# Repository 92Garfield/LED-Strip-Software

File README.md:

# gLED — WLAN LED Strip

NeoPixel strip on a Raspberry Pi Pico W (CircuitPython 9), controlled via browser extension.

## Folders

- `firmware/GEdge` — CIRCUITPY drive content (kitchen strip, 150 LEDs, `192.168.2.42`)
- `gLED-Client Chrome` — Chrome extension, **source of truth** for client `js/` + `css/`
- `gLED-Client Firefox` — Firefox extension (desktop + Android), only `manifest.json` differs
- `client/GEdge-html` — old on-controller web client (retired, kept for reference)

## Firmware (`firmware/GEdge`)

- Copy `src/config.example.py` to `src/config.py`, then set WiFi, IP, LED count, name, physical layout, and default animation
- `src/led_server.py` — HTTP server; serves one tiny HTML page exposing global `gLED`
- `src/animation_runner.py` — non-blocking animation loop beside the server
- `animations/*.py` — one class `Animation` per file (`start(now)` / `step(now)`)
  - `hue_cycle` — whole strip, hue rotates (interval + step configurable)
  - `fill_runner` — red runner right→left stacks until full, then back to blue
- `glib/color.py` — `hsv_to_rgb()` for NeoPixel
- Boot: connects WiFi, starts server, autostarts `config.DEFAULT_ANIMATION`

## HTTP API (`POST /data`, urlencoded, values NOT percent-encoded)

- `type=set` `data=r,g,b|r,g,b|…` — set all pixels (stops animation)
- `type=brightness` `data=1..100`
- `type=animation` `data=<name>` or `data=stop`
- `GET /` — HTML with `var gLED = {name, ledCount, length, physical, animations}`

## Clients (extensions)

- Run on the controller page, replace it entirely with their own UI
- Custom elements (`js/elements/`), built by `js/app.js`, dark CSS
- Show physical layout (y-up), tabs: Animation / Manual (tap LEDs to paint)
- No live data from server; last set state kept in `localStorage`
- Brightness slider in header

### Chrome

- `chrome://extensions` → Developer mode → Load unpacked → `gLED-Client Chrome`

### Firefox (desktop + Android)

- After client changes: run `gLED-Client Firefox/sync.ps1` (copies `js/`+`css/` from Chrome)
- Desktop test: `about:debugging` → Load Temporary Add-on
- Android: needs signed `.xpi` via addons.mozilla.org (unlisted) — see `gLED-Client Firefox/README.md`

## New controller / IP change

Update the IP in **3 places**:

- `gLED-Client Chrome/manifest.json` → `matches`
- `gLED-Client Firefox/manifest.json` → `matches` **and** `host_permissions`
- Firmware: `src/config.py` → `STATIC_IP`

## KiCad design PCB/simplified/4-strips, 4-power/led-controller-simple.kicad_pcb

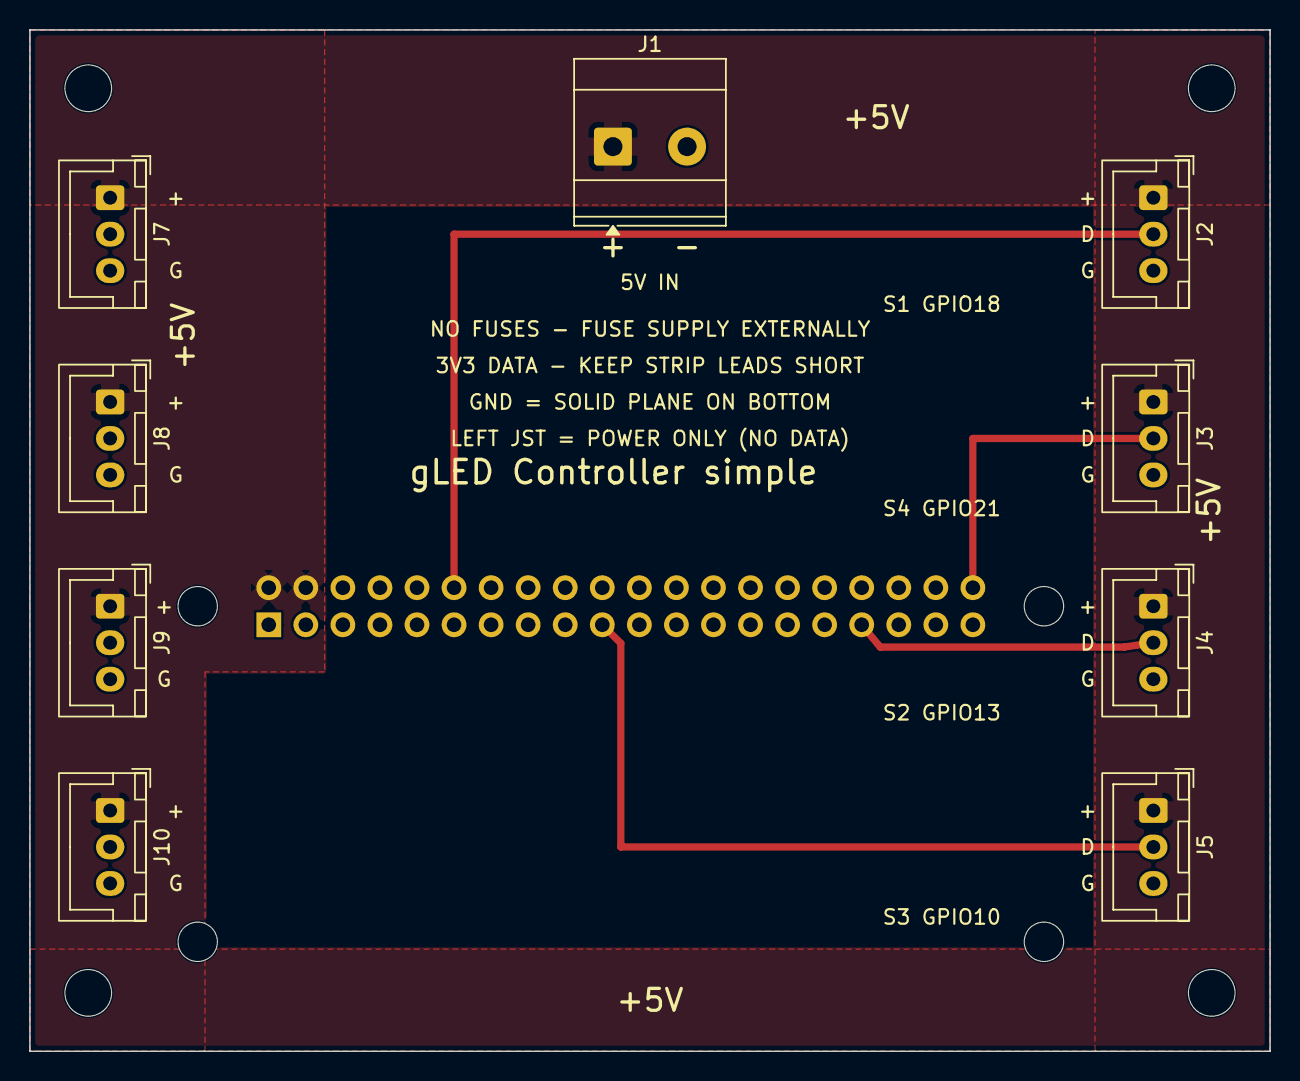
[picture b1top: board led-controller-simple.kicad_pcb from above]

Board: 2 copper layers, 85.0 x 70.0 mm, 18 parts (1 on the bottom side), 6 nets.

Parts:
H1, H2, H3, H4: MountingHole_2.7mm_M2.5
H5, H6, H7, H8: MountingHole_3.2mm_M3
J1: 5V IN; TerminalBlock_Phoenix_MKDS-3-2-5.08_1x02_P5.08mm_Horizontal
J2: GPIO18; JST_XH_B3B-XH-A_1x03_P2.50mm_Vertical
J3: GPIO21; JST_XH_B3B-XH-A_1x03_P2.50mm_Vertical
J4: GPIO13; JST_XH_B3B-XH-A_1x03_P2.50mm_Vertical
J5: GPIO10; JST_XH_B3B-XH-A_1x03_P2.50mm_Vertical
J6: Pi Zero 2 WH; PinSocket_2x20_P2.54mm_Vertical
J7, J8, J9, J10: PWR; JST_XH_B3B-XH-A_1x03_P2.50mm_Vertical

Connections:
+5V: J1.1, J2.1, J3.1, J4.1, J5.1, J6.2, J6.4, J7.1, J8.1, J9.1, J10.1
DATA_GPIO10: J5.2, J6.19
DATA_GPIO13: J4.2, J6.33
DATA_GPIO18: J2.2, J6.12
DATA_GPIO21: J3.2, J6.40
GND: J1.2, J2.3, J3.3, J4.3, J5.3, J6.6, J6.9, J6.14, J6.20, J6.25, J6.30, J6.34, J6.39, J7.3, J8.3, J9.3, J10.3

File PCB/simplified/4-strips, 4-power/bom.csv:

Comment,Designator,Footprint,Quantity,LCSC Part #,Notes
Screw terminal 5.08mm 2P (KF301-5.0-2P),J1,TB-5.08-2P,1,C474881,5V power input; mark +/- on silkscreen
JST XH 3-pin header (B3B-XH-A),"J2,J3,J4,J5,J7,J8,J9,J10",JST-XH-3P vertical THT,8,C144394,"J2-J5: strip outputs +5V / DATA / GND; J7-J10: power only (+5V / GND, data pin unconnected)"
Female header 2x20 2.54mm,J6,PinSocket 2x20 P2.54mm,1,C2977589,Socket for Pi Zero 2 WH; solder on the BACK side
M2.5 standoff + screws,"H1-H4",,4,,Not on the PCB; mounts the Pi under the board

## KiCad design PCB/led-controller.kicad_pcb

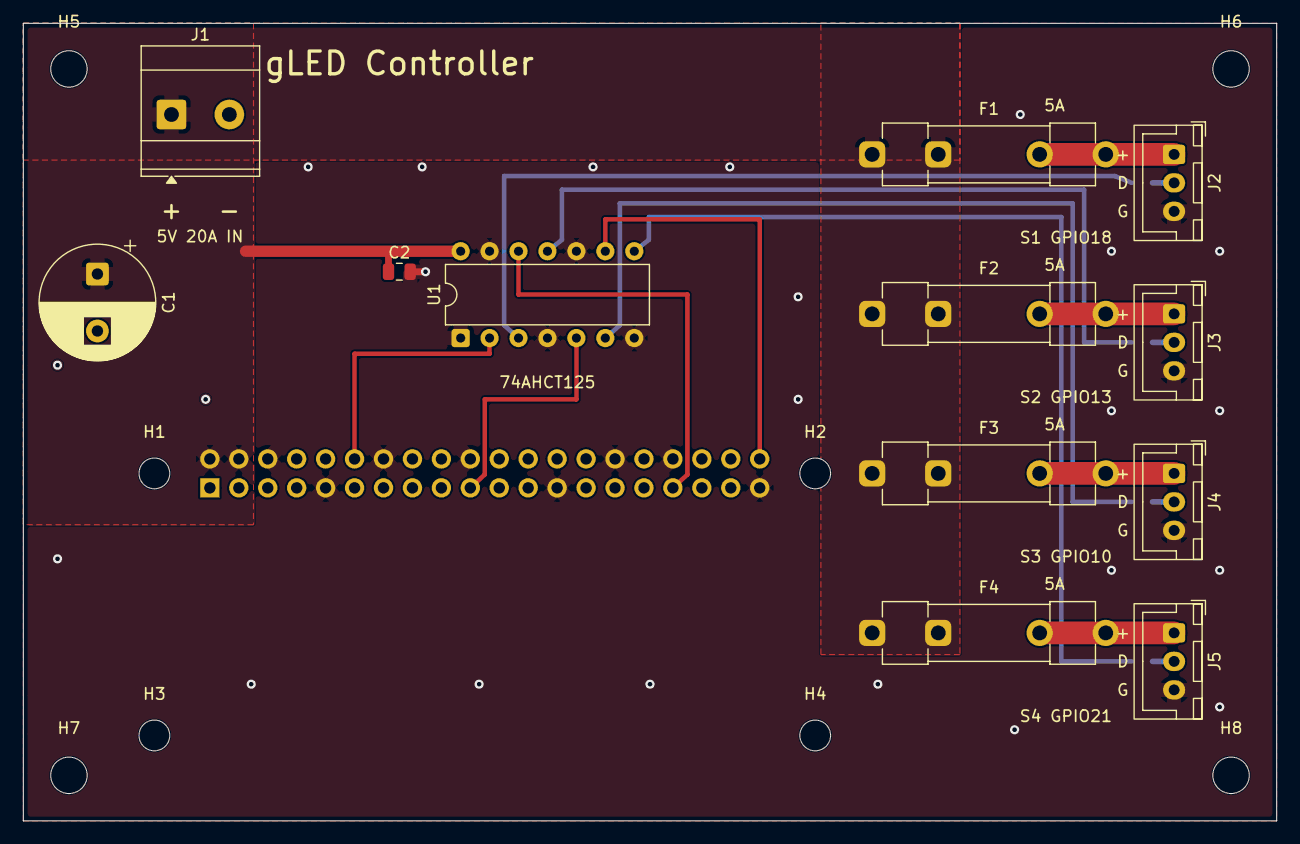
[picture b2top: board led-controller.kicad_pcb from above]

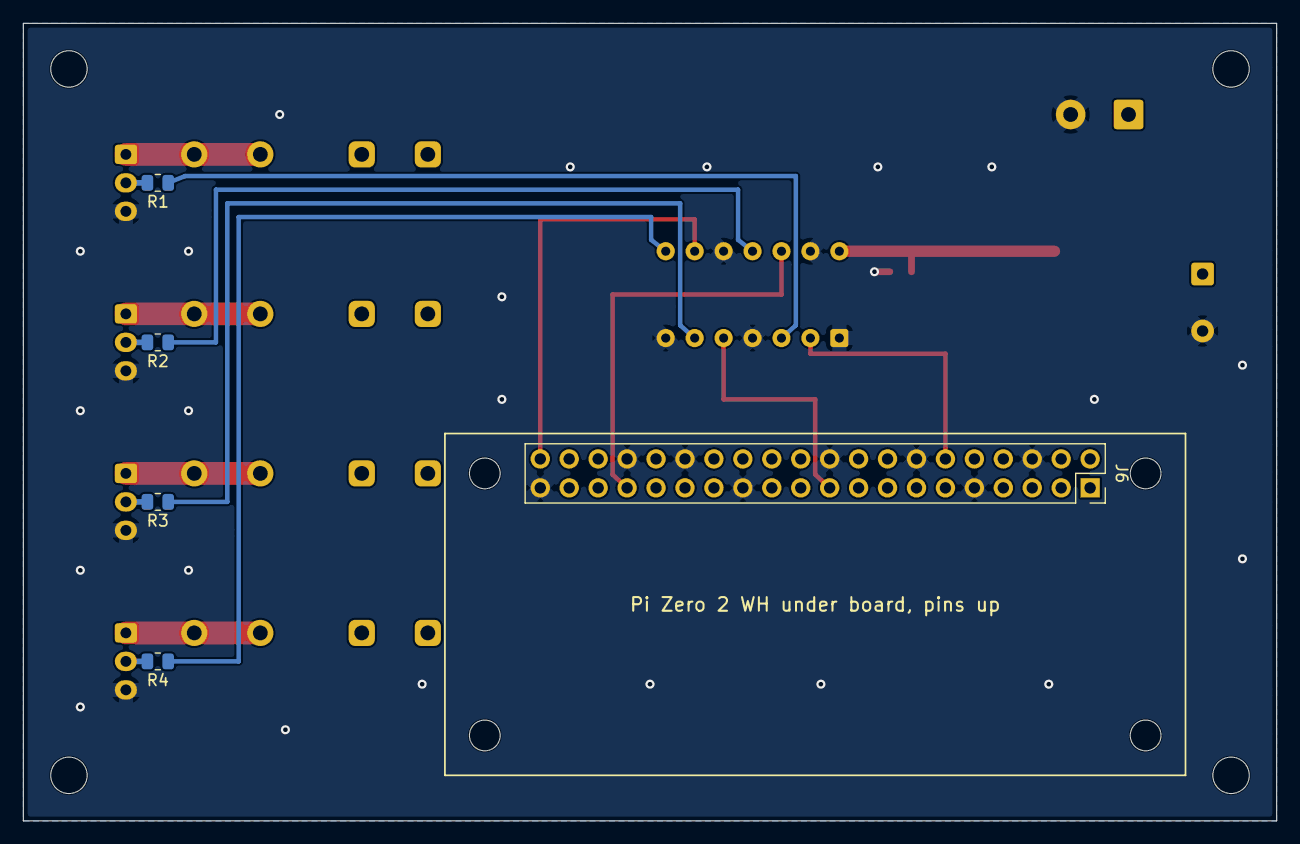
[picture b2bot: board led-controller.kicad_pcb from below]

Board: 2 copper layers, 110.0 x 70.0 mm, 25 parts (5 on the bottom side), 18 nets.

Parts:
C1: 1000uF 16V; CP_Radial_D10.0mm_P5.00mm
C2: 100nF; C_0805_2012Metric
F1, F2, F3, F4: 5A; Fuseholder_Clip-5x20mm_Littelfuse_520_Inline_P20.50x5.80mm_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
H1, H2, H3, H4: MountingHole_2.7mm_M2.5
H5, H6, H7, H8: MountingHole_3.2mm_M3
J1: 5V IN; TerminalBlock_Phoenix_MKDS-3-2-5.08_1x02_P5.08mm_Horizontal
J2: STRIP1; JST_XH_B3B-XH-A_1x03_P2.50mm_Vertical
J3: STRIP2; JST_XH_B3B-XH-A_1x03_P2.50mm_Vertical
J4: STRIP3; JST_XH_B3B-XH-A_1x03_P2.50mm_Vertical
J5: STRIP4; JST_XH_B3B-XH-A_1x03_P2.50mm_Vertical
J6: Pi Zero 2 WH; PinSocket_2x20_P2.54mm_Vertical
R1, R2, R3, R4: 470R; R_0805_2012Metric
U1: 74AHCT125; DIP-14_W7.62mm

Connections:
5V_S1: F1.2, J2.1
5V_S2: F2.2, J3.1
5V_S3: F3.2, J4.1
5V_S4: F4.2, J5.1
+5V: C1.1, C2.1, F1.1, F2.1, F3.1, F4.1, J1.1, J6.2, J6.4, U1.14
D1_5V: R1.1, U1.3
D2_5V: R2.1, U1.11
D3_5V: R3.1, U1.6
D4_5V: R4.1, U1.8
D10_3V3: J6.19, U1.5
D13_3V3: J6.33, U1.12
D18_3V3: J6.12, U1.2
D21_3V3: J6.40, U1.9
DATA1: J2.2, R1.2
DATA2: J3.2, R2.2
DATA3: J4.2, R3.2
DATA4: J5.2, R4.2
GND: C1.2, C2.2, J1.2, J2.3, J3.3, J4.3, J5.3, J6.6, J6.9, J6.14, J6.20, J6.25, J6.30, J6.34, J6.39, U1.1, U1.4, U1.7, U1.10, U1.13

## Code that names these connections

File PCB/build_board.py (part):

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N_5V   = net("+5V")
N_GND  = net("GND")
N_5V_S = [net(f"5V_S{i}") for i in (1, 2, 3, 4)]          # fused strip supplies
N_GPIO = [net(n) for n in ("D18_3V3", "D13_3V3", "D10_3V3", "D21_3V3")]
N_D5V  = [net(f"D{i}_5V") for i in (1, 2, 3, 4)]          # buffer out -> resistor
N_DATA = [net(f"DATA{i}") for i in (1, 2, 3, 4)]          # resistor -> JST

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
